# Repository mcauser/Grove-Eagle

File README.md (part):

# Grove-Eagle
[Eagle](http://www.cadsoftusa.com/) source files for [Grove](http://www.seeedstudio.com/wiki/GROVE_System) modules

Module | Latest | Wiki | Bazaar | SKU
:----- |:------ |:---- |:------ |:---
Grove - 125KHz RFID Reader | - | [Wiki](http://www.seeedstudio.com/wiki/Grove_-_125KHz_RFID_Reader) | [Buy](http://www.seeedstudio.com/depot/Grove-125KHz-RFID-Reader-p-1008.html) | SEN11425P
Grove - 2-Coil Latching Relay | v1.0b | [Wiki](http://www.seeedstudio.com/wiki/Grove_-_2-Coil_Latching_Relay) | [Buy](http://www.seeedstudio.com/depot/Grove-2Coil-Latching-Relay-p-1446.html) | COM05061P
Grove - 3-Axis Analog Accelerometer | v1.1 | [Wiki](http://www.seeedstudio.com/wiki/Grove_-_3-Axis_Analog_Accelerometer) | [Buy](http://www.seeedstudio.com/depot/Grove-3Axis-Analog-Accelerometer-p-1086.html) | SEN02241P
Grove - 3-Axis Digital Accelerometer(±1.5g) | v1.2b | [Wiki](http://www.seeedstudio.com/wiki/Grove_-_3-Axis_Digital_Accelerometer%28%C2%B11.5g%29) | [Buy](http://www.seeedstudio.com/depot/Grove-3Axis-Digital-Accelerometer15g-p-765.html) | SEN21853P
Grove - 3-Axis Digital Accelerometer(±16g) | v1.3 | [Wiki](http://www.seeedstudio.com/wiki/Grove_-_3-Axis_Digital_Accelerometer%28%C2%B116g%29) | [Buy](http://www.seeedstudio.com/depot/Grove-3Axis-Digital-Accelerometer16g-p-1156.html) | SEN04051P
Grove - 3-Axis Digital Accelerometer(±400g) | v1.0 | [Wiki](http://www.seeedstudio.com/wiki/Grove_-_3-Axis_Digital_Accelerometer%28%C2%B1400g%29) | [Buy](http://www.seeedstudio.com/depot/Grove-3Axis-Digital-Accelerometer400g-p-1897.html) | 811022001
Grove - 3-Axis Digital Compass | v1.2 | [Wiki](http://www.seeedstudio.com/wiki/Grove_-_3-Axis_Digital_Compass) | [Buy](http://www.seeedstudio.com/depot/Grove-3Axis-Digital-Compass-p-759.html) | SEN12753P
Grove - 3-Axis Digital Gyro | v1.2b | [Wiki](http://www.seeedstudio.com/wiki/Grove_-_3-Axis_Digital_Gyro) | [Buy](http://www.seeedstudio.com/depot/Grove-3Axis-Digital-Gyro-p-750.html) | SEN11763P
Grove - 315MHz Simple RF Link Kit | - | [Wiki](http://www.seeedstudio.com/wiki/Grove_-_315MHz_Simple_RF_Link_Kit) | [Buy](http://www.seeedstudio.com/depot/Grove-315MHz-Simple-RF-Link-Kit-p-1061.html) | WLS01051O
Grove - 4-Digit Display | v1.0 | [Wiki](http://www.seeedstudio.com/wiki/Grove_-_4-Digit_Display) | [Buy](http://www.seeedstudio.com/depot/Grove-4Digit-Display-p-1198.html) | LED05291P
Grove - 433MHz Simple RF Link Kit | - | [Wiki](http://www.seeedstudio.com/wiki/Grove_-_433MHz_Simple_RF_Link_Kit) | [Buy](http://www.seeedstudio.com/depot/Grove-433MHz-Simple-RF-link-kit-p-1062.html) | WLS01052O
Grove - 6-Axis Accelerometer and Compass | v2.0 | [Wiki](http://www.seeedstudio.com/wiki/Grove_-_6-Axis_Accelerometer%26Compass_V2.0) | [Buy](http://www.seeedstudio.com/depot/Grove-6Axis-AccelerometerCompass-p-1448.html) | SEN05072P
Grove - 80cm Infrared Proximity Sensor | - | [Wiki](http://www.seeedstudio.com/wiki/Grove_-_80cm_Infrared_Proximity_Sensor) | [Buy](http://www.seeedstudio.com/depot/Grove-80cm-Infrared-Proximity-Sensor-p-788.html) | SEN39046P
Grove - Air Quality Sensor | v1.3 | [Wiki](http://www.seeedstudio.com/wiki/Grove_-_Air_Quality_Sensor) | [Buy](http://www.seeedstudio.com/depot/Grove-Air-quality-sensor-p-1065.html) | SEN01111P
Grove - Alcohol Sensor | v1.2 | [Wiki](http://www.seeedstudio.com/wiki/Grove_-_Alcohol_Sensor) | [Buy](http://www.seeedstudio.com/depot/Grove-Alcohol-Sensor-p-764.html) | SEN21723P
Grove - Barometer (High-Accuracy) | v1.0 | [Wiki](http://www.seeedstudio.com/wiki/Grove_-_Barometer_%28High-Accuracy%29) | [Buy](http://www.seeedstudio.com/depot/Grove-Barometer-HighAccuracy-p-1865.html) | 811027001
Grove - Barometer Sensor (BMP180) | v1.0 | [Wiki](http://www.seeedstudio.com/wiki/Grove_-_Barometer_Sensor_%28BMP180%29) | [Buy](http://www.seeedstudio.com/depot/Grove-Barometer-SensorBMP180-p-1840.html) | 811024001
Grove - Barometer Sensor | v1.0b | [Wiki](http://www.seeedstudio.com/wiki/Grove_-_Barometer_Sensor) | [Buy](http://www.seeedstudio.com/depot/Grove-Barometer-Sensor-p-1199.html) | SEN05291P
Grove - Base Shield for IOIO-OTG | v1.0 | [Wiki](http://www.seeedstudio.com/wiki/Grove_-_Base_Shield_for_IOIO-OTG) | [Buy](http://www.seeedstudio.com/depot/Grove-Base-Shield-for-IOIOOTG-p-1613.html) | SLD00100P
Grove - Base Shield for NodeMCU | v1.0 | [Wiki](http://www.seeedstudio.com/wiki/Grove_Base_Shield_for_NodeMCU_V1.0) | [Buy](http://www.seeedstudio.com/depot/Grove-Base-Shield-for-NodeMCU-p-2513.html) | 105020008
Grove - Base Shield v1.2 | v1.2 | [Wiki](http://www.seeedstudio.com/wiki/Grove_-_Base_Shield_v1.2) | [Buy](http://www.seeedstudio.com/depot/Grove-Base-Shield-p-754.html) | SLD12148P
Grove - Base Shield v1.3 | v1.3 | [Wiki](http://www.seeedstudio.com/wiki/Grove_-_Base_Shield_V1.3) | [Buy](http://www.seeedstudio.com/depot/base-shield-v13-p-1378.html) | SLD01099P
Grove - Base Shield v2 | v2.0 | [Wiki](http://www.seeedstudio.com/wiki/Base_shield_v2) | [Buy](http://www.seeedstudio.com/depot/base-shield-v13-p-1378.html) | SLD01099P
Grove - Bee Socket | v0.9a | [Wiki](http://www.seeedstudio.com/wiki/Grove_-_Bee_Socket) | [Buy](http://www.seeedstudio.com/depot/Grove-Bee-Socket-p-1449.html) | COM05081P
Grove - BLE | v1.0 | [Wiki](http://www.seeedstudio.com/wiki/Grove_BLE_v1) | [Buy](http://www.seeedstudio.com/depot/Grove-BLE-p-1929.html) | 811007001
Grove - BLE (Dual Model) | v1.0 | [Wiki](http://www.seeedstudio.com/wiki/Grove_-_BLE_%28dual_model%29_v1.0) | [Buy](http://www.seeedstudio.com/depot/Grove-BLE-dual-model-p-2407.html) | 113020009
Grove - BlinkM | - | [Wiki](http://www.seeedstudio.com/wiki/Grove_-_BlinkM) | [Buy](http://www.seeedstudio.com/depot/Grove-BlinkM-p-826.html) | LED42149P
Grove - Blue LED | - | [Wiki](http://www.seeedstudio.com/wiki/Grove_-_LED) | [Buy](http://www.seeedstudio.com/depot/Grove-Blue-LED-p-1139.html) | COM04051P
Grove - Button | v1.0b | [Wiki](http://www.seeedstudio.com/wiki/Grove_-_Button) | [Buy](http://www.seeedstudio.com/depot/Grove-Button-p-766.html) | COM22242P
Grove - Button(P) | - | [Wiki](http://www.seeedstudio.com/wiki/Grove_-_Button) | [Buy](http://www.seeedstudio.com/depot/Grove-ButtonP-p-1243.html) | COM08211P
Grove - Buzzer | v1.1b | [Wiki](http://www.seeedstudio.com/wiki/Grove_-_Buzzer) | [Buy](http://www.seeedstudio.com/depot/Grove-Buzzer-p-768.html) | COM22458P
Grove - Chainable RGB LED | v0.9b | [Wiki](http://www.seeedstudio.com/wiki/Grove_-_Chainable_RGB_LED) | [Buy](http://www.seeedstudio.com/depot/Grove-Chainable-RGB-LED-p-850.html) | COM53140P
Grove - Chest Strap Heart Rate Sensor | v1.0 | [Wiki](http://www.seeedstudio.com/wiki/Grove_-_Chest_Strap_Heart_Rate_Sensor) | [Buy](http://www.seeedstudio.com/depot/Grove-Chest-Strap-Heart-Rate-Sensor-p-1115.html) | MED03211P
Grove - Circular LED | v0.9b | [Wiki](http://www.seeedstudio.com/wiki/Grove_-_Circular_LED) | [Buy](http://www.seeedstudio.com/depot/Grove-Circular-LED-p-1353.html) | LED01113P
Grove - CO2 Sensor | - | [Wiki](http://www.seeedstudio.com/wiki/Grove_-_CO2_Sensor) | [Buy](http://www.seeedstudio.com/depot/Grove-CO2-Sensor-p-1863.html) | 101020067
Grove - Collision Sensor | v2.0 | [Wiki](http://www.seeedstudio.com/wiki/Grove_-_Collision_Sensor) | [Buy](http://www.seeedstudio.com/depot/Grove-Collision-Sensor-p-1132.html) | SEN03281P
Grove - Differential Amplifier | v1.2 | [Wiki](http://www.seeedstudio.com/wiki/Grove_-_Differential_Amplifier) | [Buy](http://www.seeedstudio.com/depot/Grove-Differential-Amplifier-p-1284.html) | COM10221P
Grove - Digital Infrared Temperature Sensor | v1.0 | [Wiki](http://www.seeedstudio.com/wiki/Grove_-_Digital_Infrared_Temperature_Sensor) | [Buy](http://www.seeedstudio.com/depot/Grove-Digital-Infrared-Temperature-Sensor-p-2385.html) | 101020077
Grove - Digital Light Sensor | v0.9b | [Wiki](http://www.seeedstudio.com/wiki/Grove_-_Digital_Light_Sensor) | [Buy](http://www.seeedstudio.com/depot/Grove-Digital-Light-Sensor-p-1281.html) | SEN10171P
Grove - DMX512 | v1.0 | [Wiki](http://www.seeedstudio.com/wiki/Grove_-_DMX512) | [Buy](http://www.seeedstudio.com/depot/Grove-DMX512-p-1447.html) | ACC05071P
Grove - Dry-Reed Relay | v1.0b | [Wiki](http://www.seeedstudio.com/wiki/Grove_-_Dry-Reed_Relay) | [Buy](http://www.seeedstudio.com/depot/Grove-DryReed-Relay-p-1412.html) | COM04071P
Grove - Dust Sensor | - | [Wiki](http://www.seeedstudio.com/wiki/Grove_-_Dust_Sensor) | [Buy](http://www.seeedstudio.com/depot/Grove-Dust-Sensor-p-1050.html) | SEN12291P
Grove - Ear-clip Heart Rate Sensor | - | [Wiki](http://www.seeedstudio.com/wiki/Grove_-_Ear-clip_Heart_Rate_Sensor) | [Buy](http://www.seeedstudio.com/depot/Grove-Earclip-Heart-Rate-Sensor-p-1116.html) | MED03212P
Grove - Electricity Sensor | v1.0 | [Wiki](http://www.seeedstudio.com/wiki/Grove_-_Electricity_Sensor) | [Buy](http://www.seeedstudio.com/depot/Grove-Electricity-Sensor-p-777.html) | SEN23931P
Grove - Electromagnet | v1.0 | [Wiki](http://www.seeedstudio.com/wiki/Grove_-_Electromagnet) | [Buy](http://www.seeedstudio.com/depot/Grove-Electromagnet-p-1820.html) | 811014001
Grove - EL Driver | v1.0 | [Wiki](http://www.seeedstudio.com/wiki/Grove_-_EL_Driver) | [Buy](http://www.seeedstudio.com/depot/GroveEL-Driver-p-2269.html) | 105020005
Grove - EMG Detector | v1.1 | [Wiki](http://www.seeedstudio.com/wiki/Grove_-_EMG_Detector) | [Buy](http://www.seeedstudio.com/depot/Grove-EMG-Detector-p-1737.html) | 811006001
Grove - Encoder | v0.9b | [Wiki](http://www.seeedstudio.com/wiki/Grove_-_Encoder) | [Buy](http://www.seeedstudio.com/depot/Grove-Encoder-p-1352.html) | COM01112P
Grove - Finger-clip Heart Rate Sensor | v1.0 | [Wiki](http://www.seeedstudio.com/wiki/Grove_-_Finger-clip_Heart_Rate_Sensor) | [Buy](http://www.seeedstudio.com/depot/Grove-Fingerclip-Heart-Rate-Sensor-p-2425.html) | 103020024
Grove - Fingerprint Sensor | - | [Wiki](http://www.seeedstudio.com/wiki/Grove_-_Fingerprint_Sensor) | [Buy](http://www.seeedstudio.com/depot/Grove-Fingerprint-Sensor-p-1424.html) | SEN04172P
Grove - Flame Sensor | v1.0 | [Wiki](http://www.seeedstudio.com/wiki/Grove_-_Flame_Sensor) | [Buy](http://www.seeedstudio.com/depot/Grove-Flame-Sensor-p-1450.html) | SEN05082P
Grove - FM Receiver | v1.0 | [Wiki](http://www.seeedstudio.com/wiki/Grove_-_FM_Receiver) | [Buy](http://www.seeedstudio.com/depot/Grove-FM-Receiver-p-1841.html) | 811021001
Grove - Gas Sensor(MQ2) | v1.4 | [Wiki](http://www.seeedstudio.com/wiki/Grove_-_Gas_Sensor%28MQ2%29) | [Buy](http://www.seeedstudio.com/depot/Grove-Gas-SensorMQ2-p-937.html) | SEN90512P
Grove - Gas Sensor(MQ3) | v1.4 | [Wiki](http://www.seeedstudio.com/wiki/Grove_-_Gas_Sensor) | [Buy](http://www.seeedstudio.com/depot/Grove-Gas-SensorMQ3-p-1418.html) | SEN04091P
Grove - Gas Sensor(MQ5) | v1.4 | [Wiki](http://www.seeedstudio.com/wiki/Grove_-_Gas_Sensor%28MQ5%29) | [Buy](http://www.seeedstudio.com/depot/Grove-Gas-SensorMQ5-p-938.html) | SEN90502P
Grove - Gas Sensor(MQ9) | v1.4 | [Wiki](http://www.seeedstudio.com/wiki/Grove_-_Gas_Sensor) | [Buy](http://www.seeedstudio.com/depot/Grove-Gas-SensorMQ9-p-1419.html) | SEN04092P
Grove - Gas Sensor(O2) | v1.0 | [Wiki](http://www.seeedstudio.com/wiki/Grove_-_Gas_Sensor%28O%E2%82%82%29) | [Buy](http://www.seeedstudio.com/depot/Grove-Gas-SensorO2-p-1541.html) | SEN00500P
Grove - Geiger Counter | v0.9b | [Wiki](http://www.seeedstudio.com/wiki/Grove_-_Geiger_Counter) | [Buy](http://www.seeedstudio.com/depot/Grove-Geiger-Counter-p-867.html) | SEN63024P
Grove - Gesture | v1.0 | [Wiki](http://www.seeedstudio.com/wiki/Grove_-_Gesture_v1.0) | [Buy](http://www.seeedstudio.com/depot/Grove-Gesture-p-2463.html) | 101020083
Grove - GPS | v1.1 | [Wiki](http://www.seeedstudio.com/wiki/Grove_-_GPS) | [Buy](http://www.seeedstudio.com/depot/Grove-GPS-p-959.html) | SEN10752P
Grove - Green LED | - | [Wiki](http://www.seeedstudio.com/wiki/Grove_-_LED) | [Buy](http://www.seeedstudio.com/depot/Grove-Green-LED-p-1144.html) | COM04053P
Grove - GSR Sensor | v1.0 | [Wiki](http://www.seeedstudio.com/wiki/Grove_-_GSR_Sensor) | [Buy](http://www.seeedstudio.com/depot/Grove-GSR-p-1614.html) | SEN01400P
Grove - Hall Sensor | v0.9b | [Wiki](http://www.seeedstudio.com/wiki/Grove_-_Hall_Sensor) | [Buy](http://www.seeedstudio.com/depot/Grove-Hall-Sensor-p-965.html) | SEN14034P
Grove - Haptic Motor | v0.9 | [Wiki](http://www.seeedstudio.com/wiki/Grove_-_Haptic_Motor) | [Buy](http://www.seeedstudio.com/depot/Grove%C2%A0%C2%A0Haptic%C2%A0Motor-p-2546.html) | 105020011
Grove - HCHO Sensor | v1.0 | [Wiki](http://www.seeedstudio.com/wiki/Grove_-_HCHO_Sensor) | [Buy](http://www.seeedstudio.com/depot/Grove-HCHO-Sensor-p-1593.html) | SEN01500P
Grove - High Temperature Sensor | v1.0 | [Wiki](http://www.seeedstudio.com/wiki/Grove_-_High_Temperature_Sensor) | [Buy](http://www.seeedstudio.com/depot/Grove-High-Temperature-Sensor-p-1810.html) | 811010001
Grove - I2C ADC | v1.0 | [Wiki](http://www.seeedstudio.com/wiki/Grove_-_I2C_ADC) | [Buy](http://www.seeedstudio.com/depot/Grove-I2C-ADC-p-1580.html) | INT00100P
Grove - I2C Color Sensor | v1.2 | [Wiki](http://www.seeedstudio.com/wiki/Grove_-_I2C_Color_Sensor) | [Buy](http://www.seeedstudio.com/depot/Grove-I2C-Color-Sensor-p-854.html) | SEN60256P
Grove - I2C FM Receiver | v1.1 | [Wiki](http://www.seeedstudio.com/wiki/Grove_-_I2C_FM_Receiver) | [Buy](http://www.seeedstudio.com/depot/Grove-I2C-FM-Receiver-p-1953.html) | 107020006
Grove - I2C Hub | v1.1 | [Wiki](http://www.seeedstudio.com/wiki/Grove_-_I2C_Hub) | [Buy](http://www.seeedstudio.com/depot/Grove-I2C-Hub-p-851.html) | ACC53133P
Grove - I2C Motor Driver | v1.2 | [Wiki](http://www.seeedstudio.com/wiki/Grove_-_I2C_Motor_Driver) | [Buy](http://www.seeedstudio.com/depot/Grove-I2C-Motor-Driver-p-907.html) | ROB72212P
Grove - I2C Touch Sensor | v1.1 | [Wiki](http://www.seeedstudio.com/wiki/Grove_-_I2C_Touch_Sensor) | [Buy](http://www.seeedstudio.com/depot/Grove-I2C-Touch-Sensor-p-840.html) | SEN51153P
Grove - IMU 9DOF | v2.0 | [Wiki](http://www.seeedstudio.com/wiki/Grove_-_IMU_9DOF) | [Buy](http://www.seeedstudio.com/depot/Grove-IMU-9DOF-p-1728.html) | 811003001
Grove - IMU 10DOF | v1.1 | [Wiki](http://www.seeedstudio.com/wiki/Grove_-_IMU_10DOF) | http://www.seeedstudio.com/depot/Grove-IMU-10DOF-p-2386.html | 101020079
Grove - Infrared Emitter | v1.1 | [Wiki](http://www.seeedstudio.com/wiki/Grove_-_Infrared_Emitter) | [Buy](http://www.seeedstudio.com/depot/Grove-Infrared-Emitter-p-993.html) | WLS12148P
Grove - Infrared Receiver | v1.0 | [Wiki](http://www.seeedstudio.com/wiki/Grove_-_Infrared_Receiver) | [Buy](http://www.seeedstudio.com/depot/Grove-Infrared-Receiver-p-994.html) | WLS12136P
Grove - Infrared Reflective Sensor | v1.0 | [Wiki](http://www.seeedstudio.com/wiki/Grove_-_Infrared_Reflective_Sensor) | [Buy](http://www.seeedstudio.com/depot/Grove-Infrared-Reflective-Sensor-p-1230.html) | WLS07061P
Grove - Infrared temperature sensor | v1.0 | [Wiki](http://www.seeedstudio.com/wiki/Grove_-_Infrared_temperature_sensor) | [Buy](http://www.seeedstudio.com/depot/Grove-Infrared-Temperature-Sensor-p-1058.html) | SEN01041P
Grove - IR Distance Interrupter | v1.0 | [Wiki](http://www.seeedstudio.com/wiki/Grove_-_IR_Distance_Interrupt) | [Buy](http://www.seeedstudio.com/depot/Grove-IR-Distance-Interrupter-p-1278.html) | SEN09281P
Grove - Joint | v2.0 | [Wiki](http://www.seeedstudio.com/wiki/Grove_-_Joint_v2.0) | - | -
Grove - LCD RGB Backlight | - | [Wiki](http://www.seeedstudio.com/wiki/Grove_-_LCD_RGB_Backlight) | [Buy](http://www.seeedstudio.com/depot/Grove-LCD-RGB-Backlight-p-1643.html) | 811004001
Grove - LED Bar | v1.0 | [Wiki](http://www.seeedstudio.com/wiki/Grove_-_LED_Bar) | [Buy](http://www.seeedstudio.com/depot/Grove-LED-Bar-p-1178.html) | LED05031P
Grove - LED Socket Kit | v1.3 | [Wiki](http://www.seeedstudio.com/wiki/Grove_-_LED_Socket_Kit) | [Buy](http://www.seeedstudio.com/depot/Grove-LED-p-767.html) | COM22341P
Grove - LED String Light | v1.0 | [Wiki](http://www.seeedstudio.com/wiki/Grove_-_LED_String_Light) | [Buy](http://www.seeedstudio.com/depot/Grove-LED-String-Light-p-1821.html) | 811019001
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
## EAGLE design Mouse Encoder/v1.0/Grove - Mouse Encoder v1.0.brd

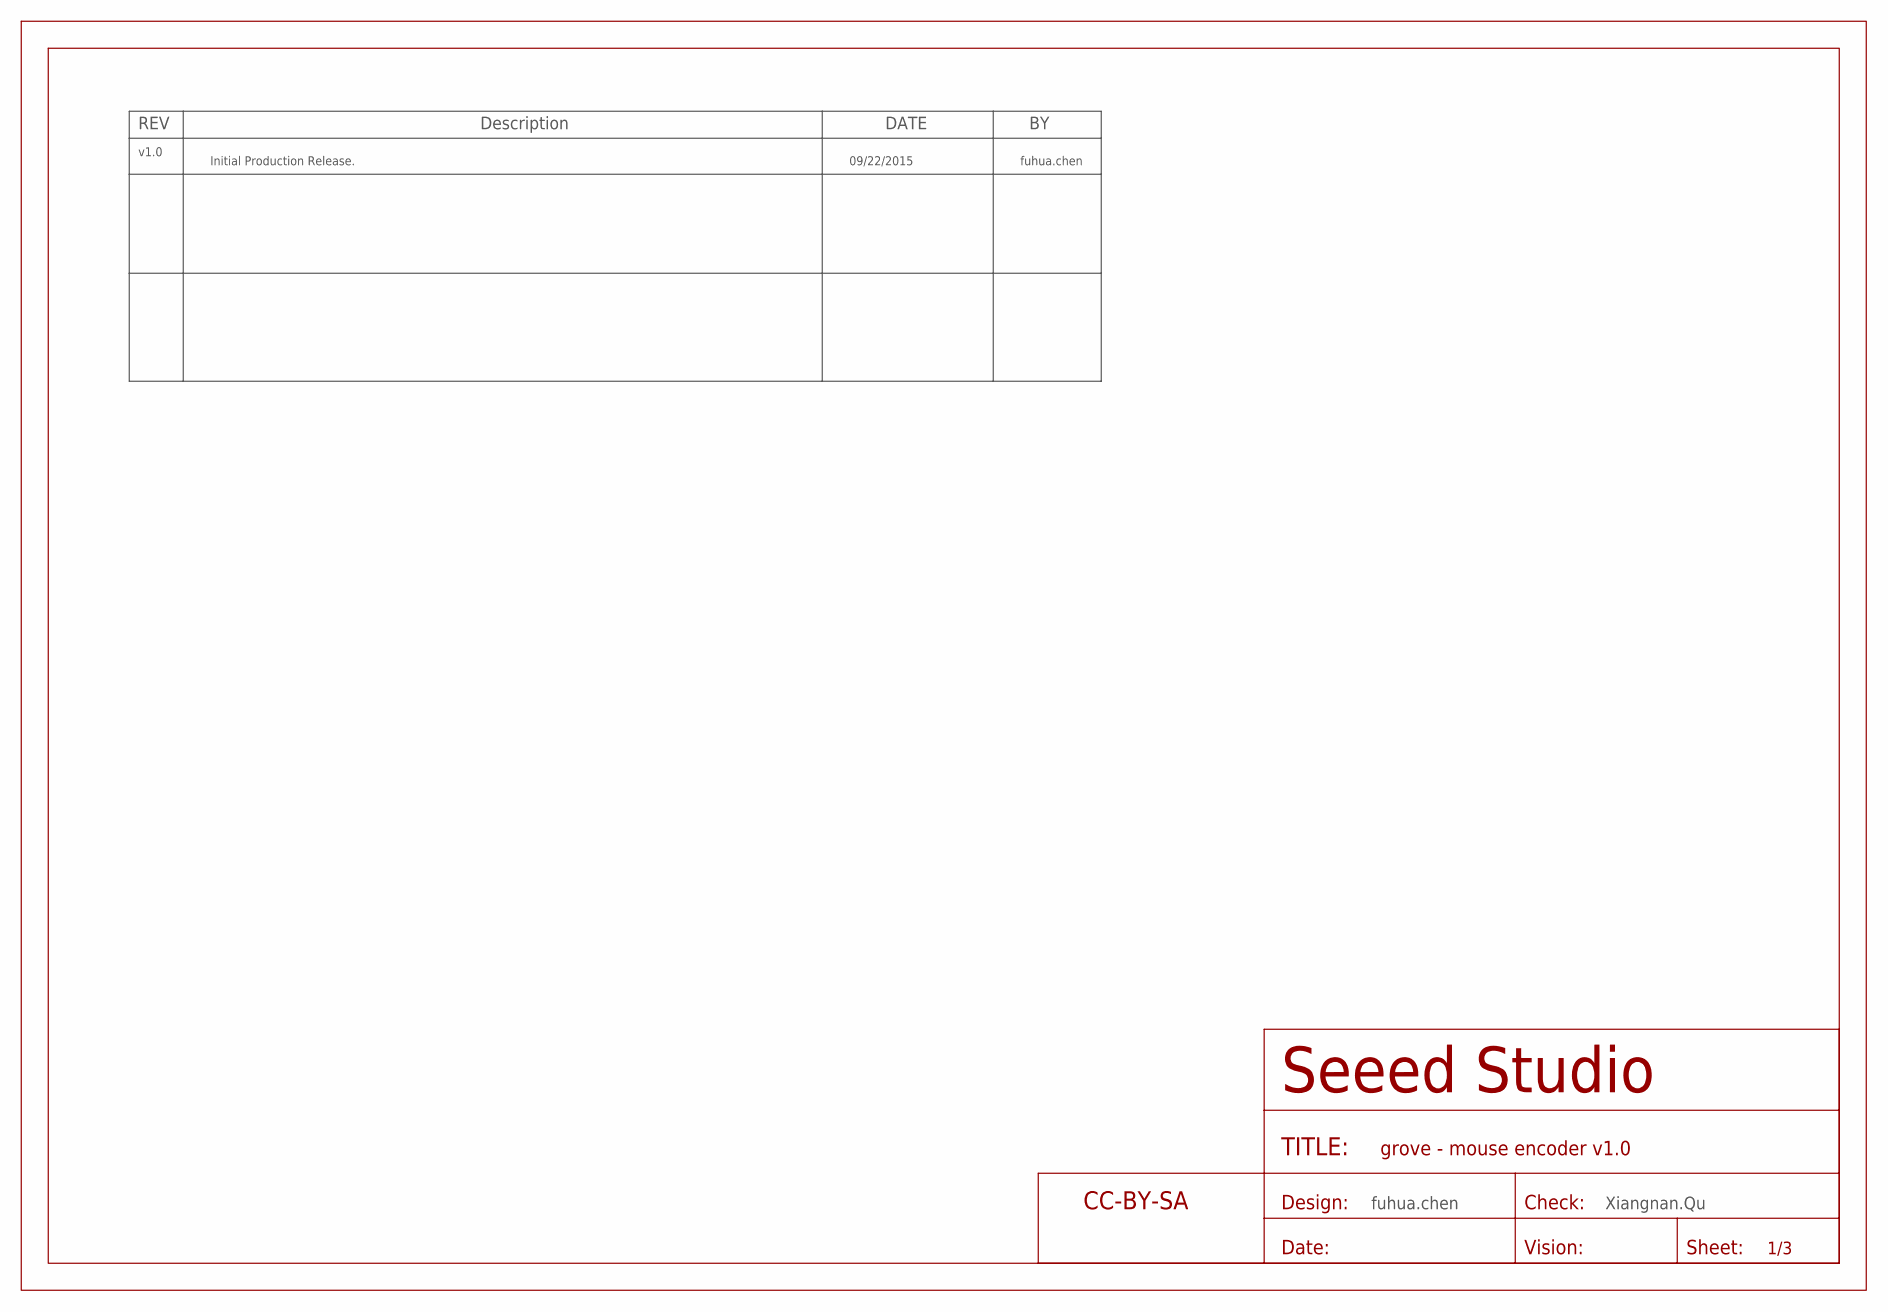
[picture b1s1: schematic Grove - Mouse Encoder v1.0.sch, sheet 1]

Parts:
U$5: SEEEDSTUDIO-OPEN-SCH-FRAME; SEEEDSTUDIO-PCB-FRAME

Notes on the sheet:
fuhua.chen
Xiangnan.Qu
REV
Description
DATE
v1.0
09/22/2015
Initial Production Release.

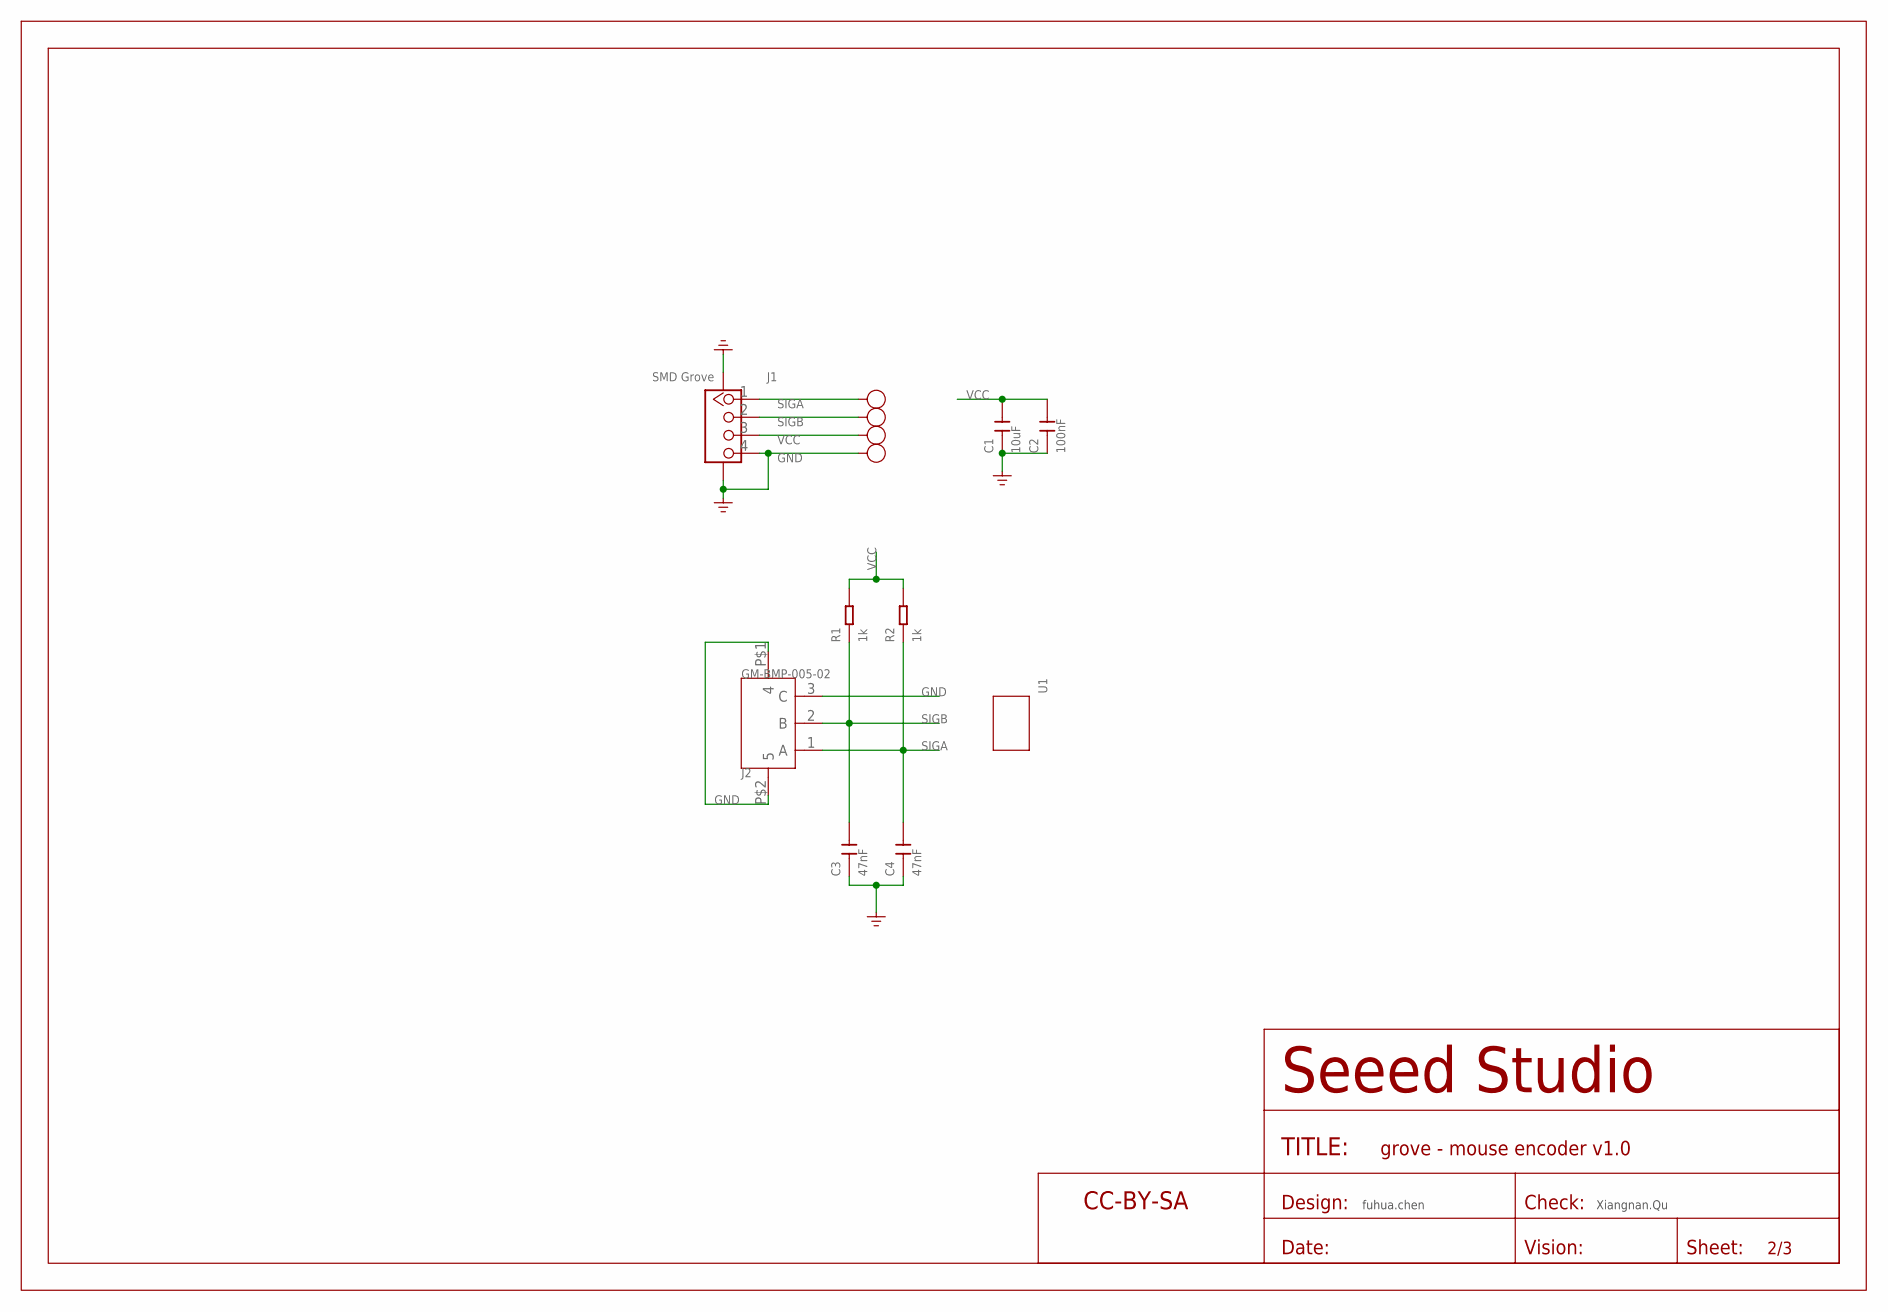
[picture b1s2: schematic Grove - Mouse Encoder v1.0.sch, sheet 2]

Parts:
C1: 10uF; C0603
C2: 100nF; C0603
C3, C4: 47nF; C0603
FR1: SEEEDSTUDIO-OPEN-SCH-FRAME; SEEEDSTUDIO-PCB-FRAME
GND: GND; TP-D45MIL
J1: SMD Grove; HW4-SMD-2.0-90D
J2: GM-BMP-005-02; DIP5-2.5-10.8X6.8X11.1MM
R1, R2: 1k; R0603
SIGA: SIGA; TP-D45MIL
SIGB: SIGB; TP-D45MIL
U1: GROVE'1U'; GROVE-1X1-TEST-PLATFORM
VCC: VCC; TP-D45MIL

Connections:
GND: C1.1, C2.1, C3.1, C4.1, GND.T, J1.4, J1.SS1, J1.SS2, J2.3 (C), J2.P$1 (4), J2.P$2 (5)
SIGA: C4.2, J1.1, J2.1 (A), R2.1, SIGA.T
SIGB: C3.2, J1.2, J2.2 (B), R1.1, SIGB.T
VCC: C1.2, C2.2, J1.3, R1.2, R2.2, VCC.T

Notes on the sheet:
fuhua.chen
Xiangnan.Qu

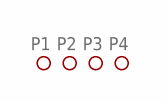
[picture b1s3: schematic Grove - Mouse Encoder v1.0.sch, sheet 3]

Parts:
P1, P2, P3, P4: PAD-MARK'ANNULAR'; ROUND-MARK-1.0

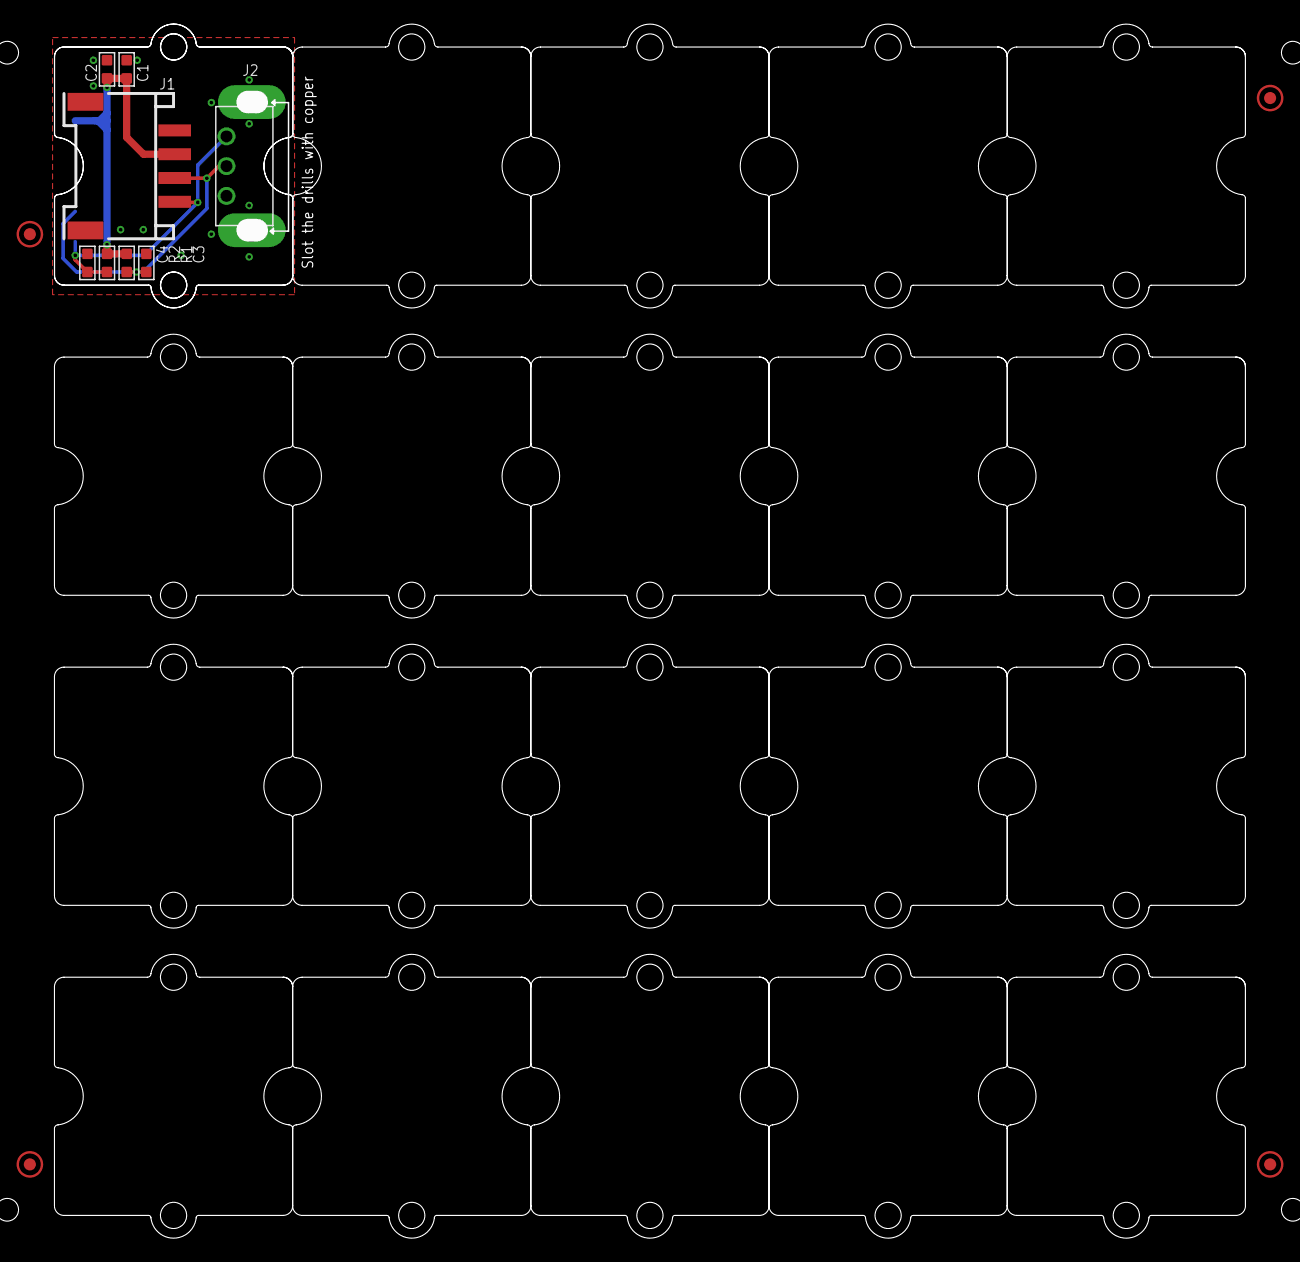
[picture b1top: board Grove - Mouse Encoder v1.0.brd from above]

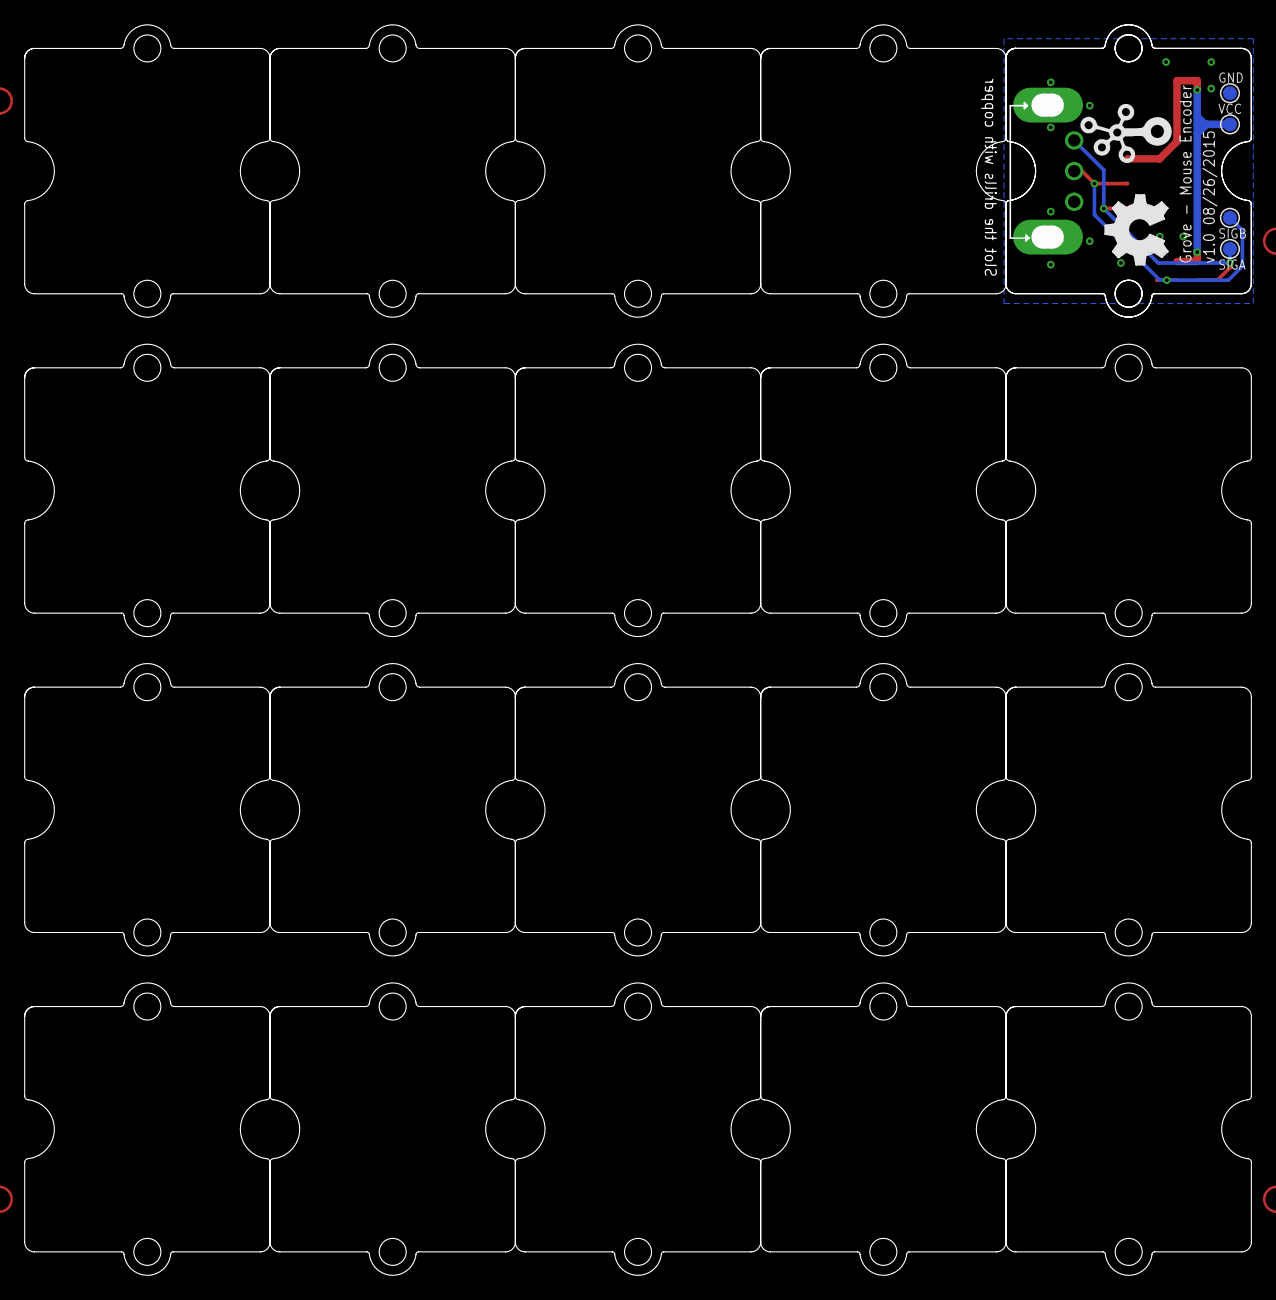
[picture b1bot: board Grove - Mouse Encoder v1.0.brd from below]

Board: 2 copper layers, 100.0 x 102.0 mm, 41 parts (6 on the bottom side), 4 nets.

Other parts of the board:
U$1: OSHW_FILLX200_NOTEXT
U$2: GROVE-SILK-BIG
U$3, U$4, U$7, U$8, U$9, U$10, U$11, U$12, U$13, U$14, U$15, U$16, U$17, U$18, U$19, U$20, U$21, U$22, U$23, U$24: GROVE-1*1-TEST-PLATFORM

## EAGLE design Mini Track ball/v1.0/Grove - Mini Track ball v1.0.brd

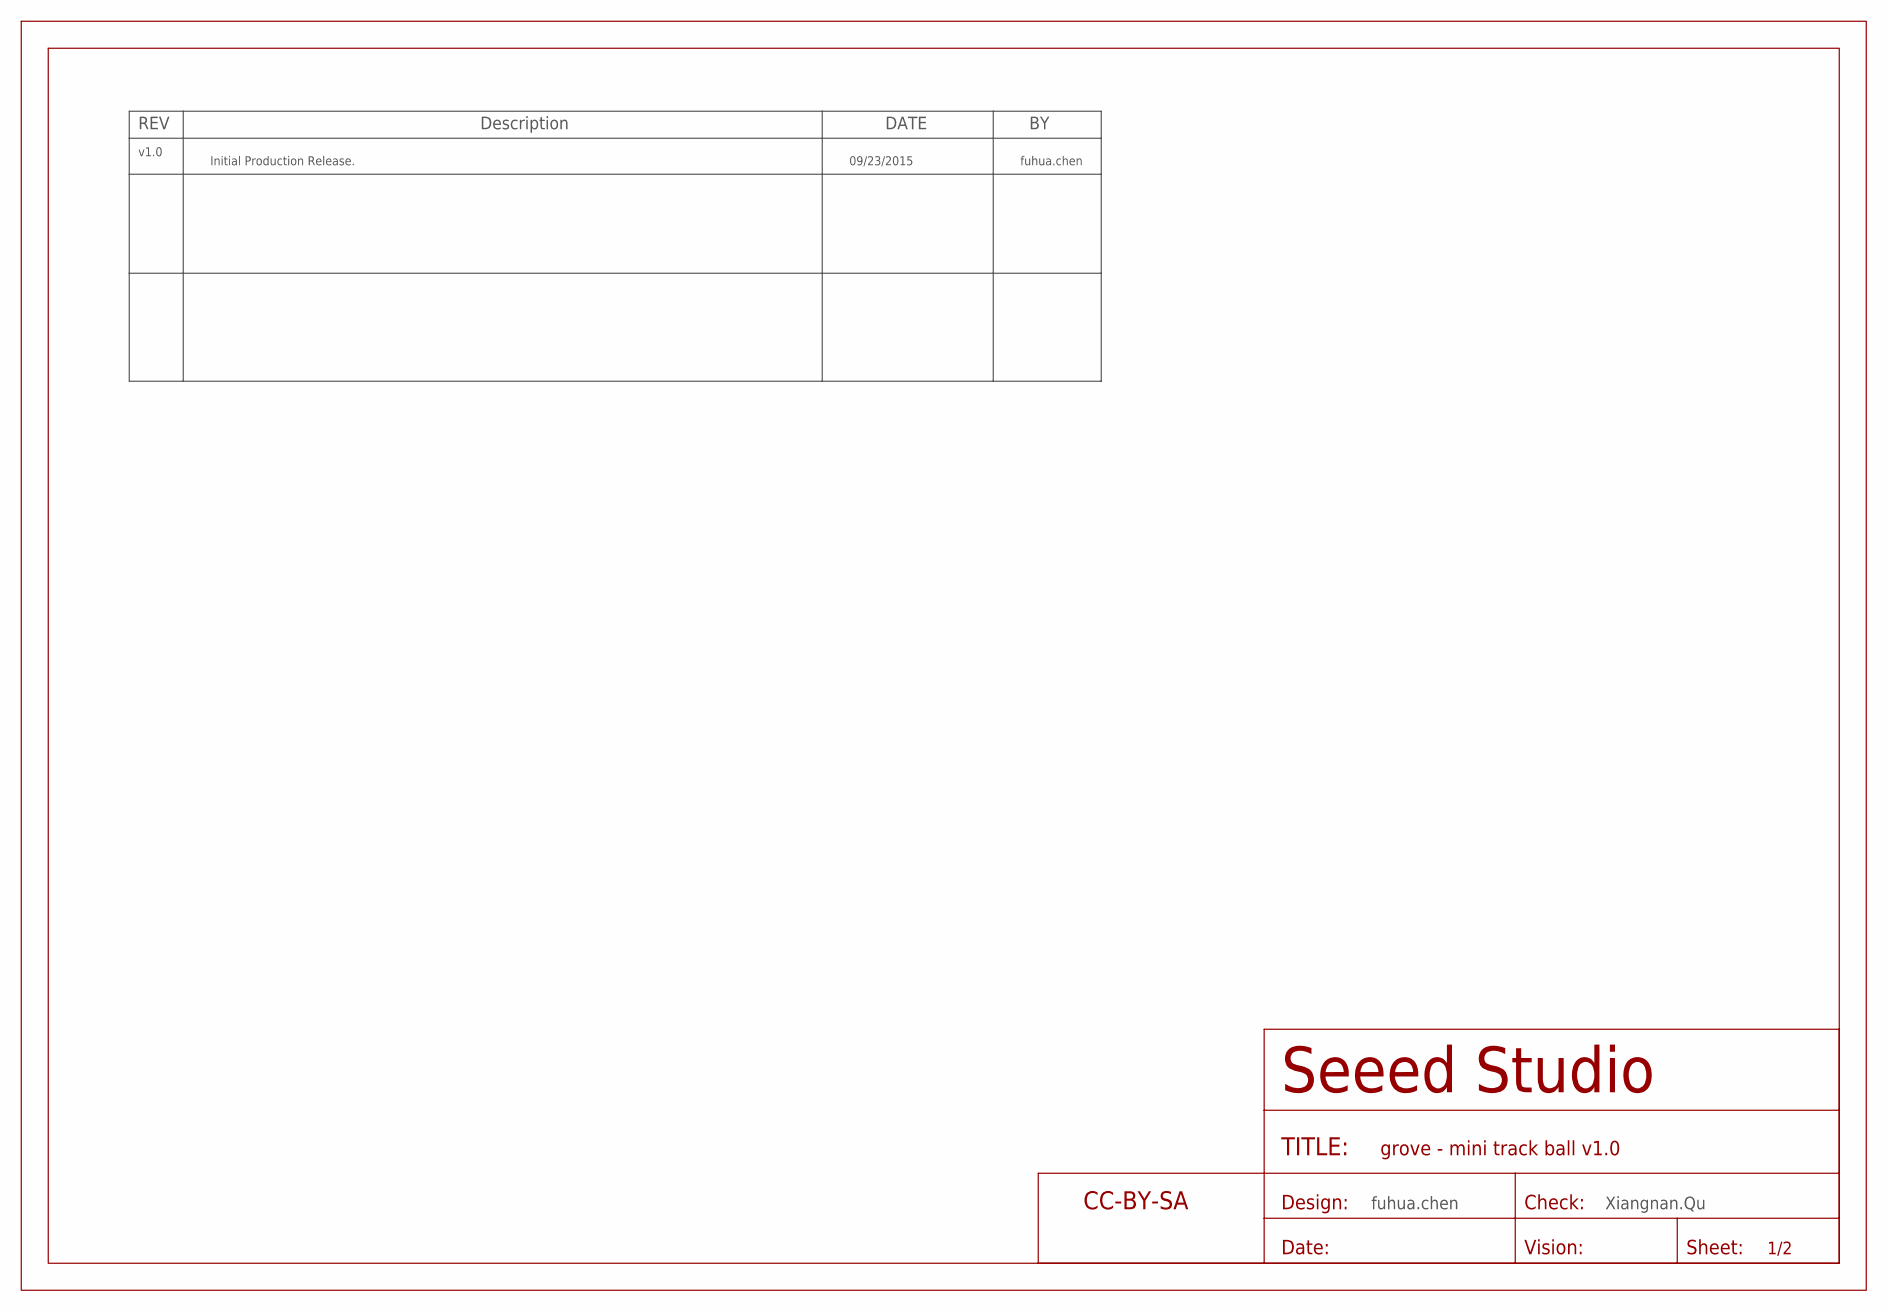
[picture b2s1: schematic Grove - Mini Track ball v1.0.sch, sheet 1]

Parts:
U$13: SEEEDSTUDIO-OPEN-SCH-FRAME; SEEEDSTUDIO-PCB-FRAME

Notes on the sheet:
fuhua.chen
Xiangnan.Qu
REV
Description
DATE
v1.0
09/23/2015
Initial Production Release.

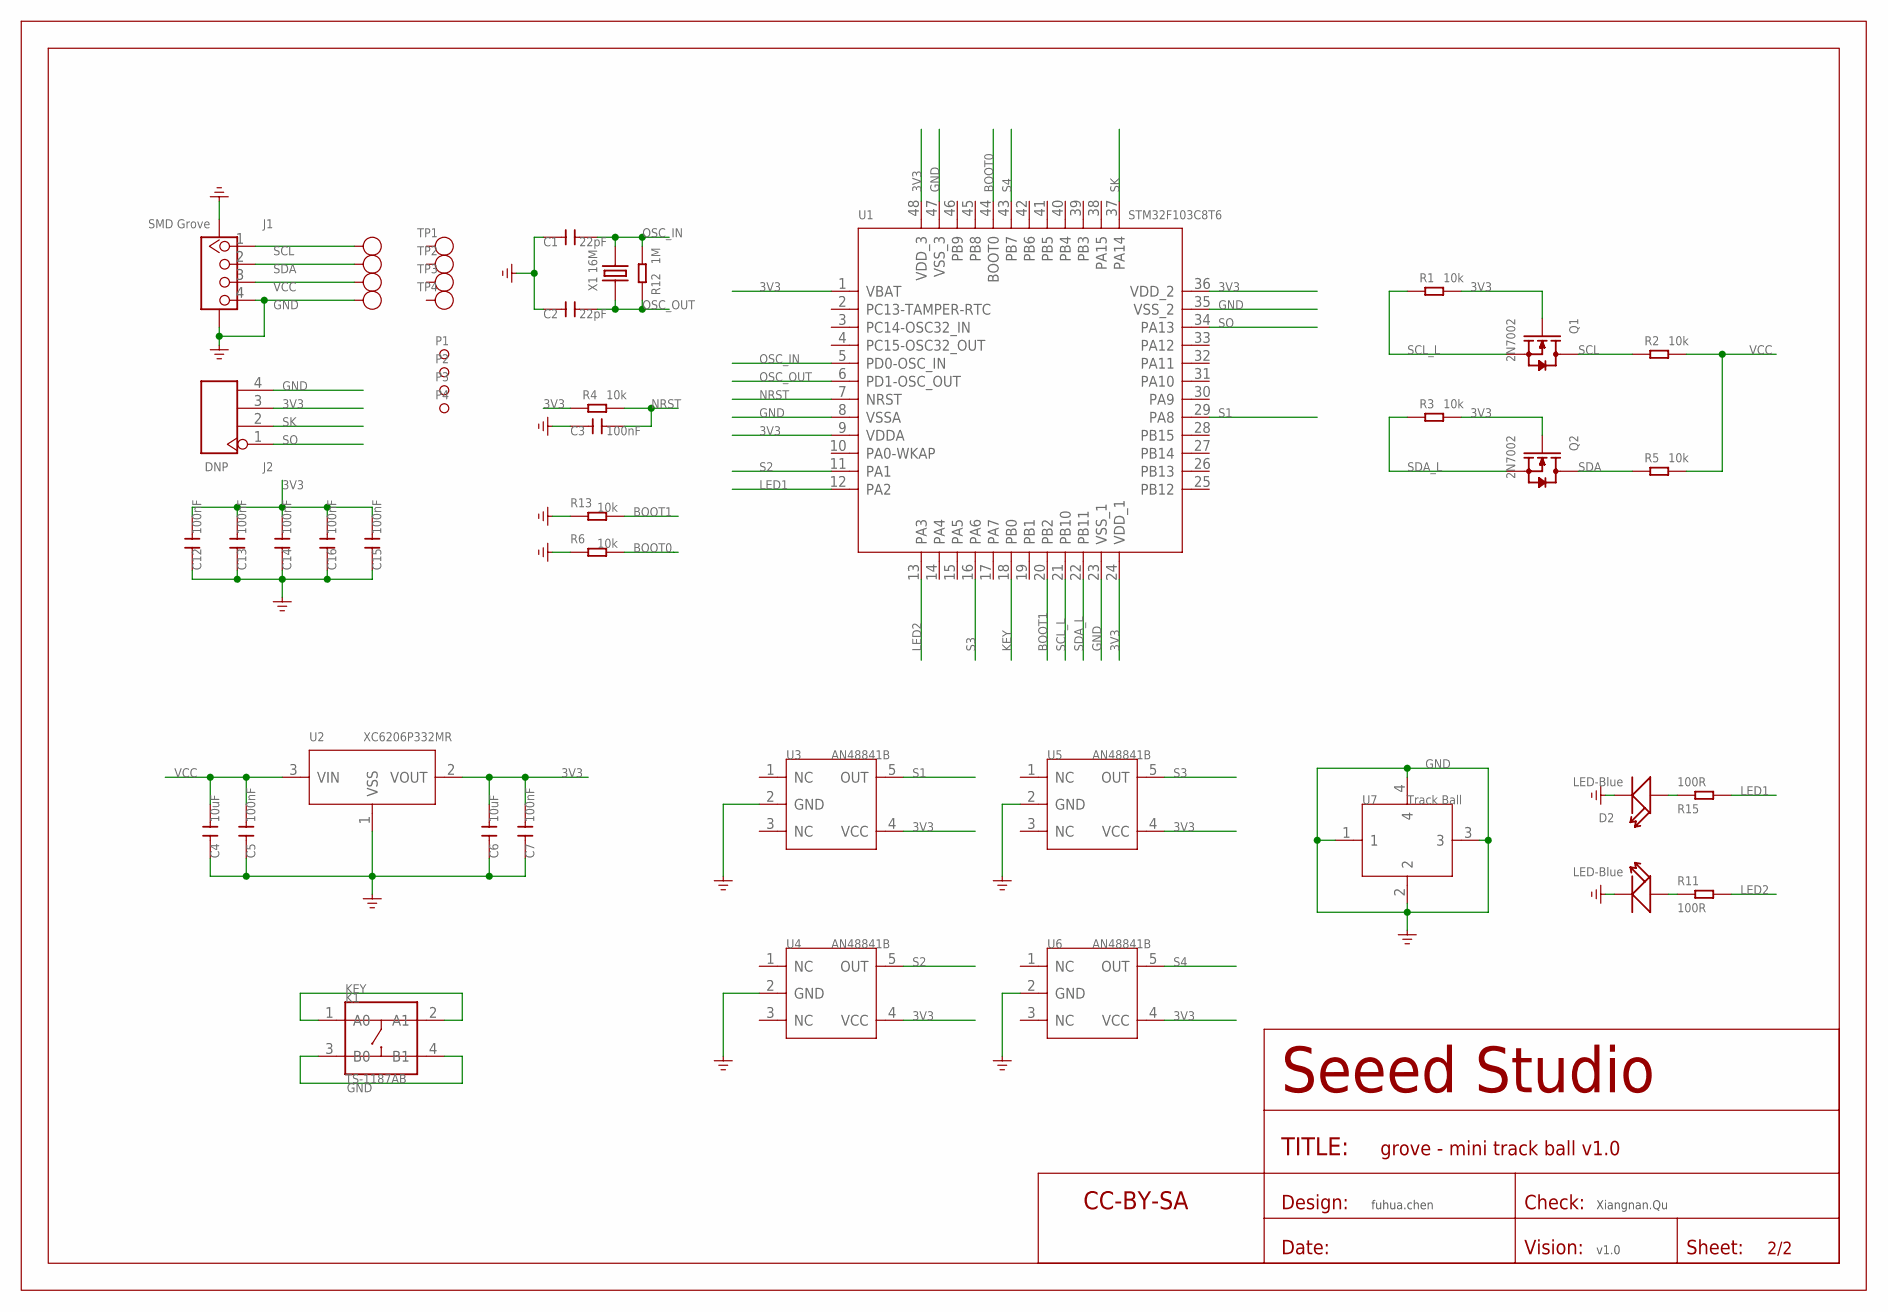
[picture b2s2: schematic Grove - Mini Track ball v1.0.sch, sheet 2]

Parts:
C1, C2: 22pF; C0402
C3, C5, C7, C12, C13, C14, C15, C16: 100nF; C0402
C4, C6: 10uF; C0402
D1, D2: LED-Blue; LED-0402
FR: SEEEDSTUDIO-OPEN-SCH-FRAME; SEEEDSTUDIO-PCB-FRAME
GND: GND; TP-D45MIL
J1: SMD Grove; HW4-SMD-2.0-90D
J2: DNP; H4-2.54
K1: TS-1187AB; SW4-4.5X4.5X0.5MM
P1, P2, P3, P4: MARK-1.0'ANNULAR'; ROUND-MARK-1.0
Q1, Q2: 2N7002; SOT-23
R1, R2, R3, R4, R5, R6, R13: 10k; R0402
R11, R15: 100R; R0402
R12: 1M; R0402
SCL: SCL; TP-D45MIL
SDA: SDA; TP-D45MIL
TP1, TP2, TP3, TP4: TEST-POINT'4545'; TP-D45MIL
U1: STM32F103C8T6; LQFP48
U2: XC6206P332MR; SOT-23
U3, U4, U5, U6: AN48841B; SMINI-5DE
U7: Track Ball; BALL4P-9.1X9.1X6.04MM
VCC: VCC; TP-D45MIL
X1: 16M; X4-SMD-3.2X2.5X0.7MM

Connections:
3V3: C6.2, C7.2, C12.2, C13.2, C14.2, C15.2, C16.2, J2.3, Q1.1 (G), Q2.1 (G), R1.2, R3.2, R4.1, U1.1 (VBAT), U1.9 (VDDA), U1.24 (VDD_1), U1.36 (VDD_2), U1.48 (VDD_3), U2.2 (VOUT), U3.4 (VCC), U4.4 (VCC), U5.4 (VCC), U6.4 (VCC)
BOOT0: R6.2, U1.44 (BOOT0)
BOOT1: R13.2, U1.20 (PB2)
GND: C1.1, C2.1, C3.1, C4.1, C5.1, C6.1, C7.1, C12.1, C13.1, C14.1, C15.1, C16.1, D1.-, D2.-, GND.T, J1.4, J1.SS1, J1.SS2, J2.4, K1.3 (B0), K1.4 (B1), R6.1, R13.1, U1.8 (VSSA), U1.23 (VSS_1), U1.35 (VSS_2), U1.47 (VSS_3), U2.1 (VSS), U3.2 (GND), U4.2 (GND), U5.2 (GND), U6.2 (GND), U7.1, U7.2, U7.3, U7.4
KEY: K1.1 (A0), K1.2 (A1), U1.18 (PB0)
LED1: R15.2, U1.12 (PA2)
LED2: R11.2, U1.13 (PA3)
unnamed: D1.+, R11.1
unnamed: D2.+, R15.1
NRST: C3.2, R4.2, U1.7 (NRST)
OSC_IN: C1.2, R12.2, U1.5 (PD0-OSC_IN), X1.4 (2)
OSC_OUT: C2.2, R12.1, U1.6 (PD1-OSC_OUT), X1.2 (1)
S1: U1.29 (PA8), U3.5 (OUT)
S2: U1.11 (PA1), U4.5 (OUT)
S3: U1.16 (PA6), U5.5 (OUT)
S4: U1.43 (PB7), U6.5 (OUT)
SCL: J1.1, Q1.3 (D), R2.1, SCL.T
SCL_L: Q1.2 (S), R1.1, U1.21 (PB10)
SDA: J1.2, Q2.3 (D), R5.1, SDA.T
SDA_L: Q2.2 (S), R3.1, U1.22 (PB11)
SK: J2.2, U1.37 (PA14)
SO: J2.1, U1.34 (PA13)
VCC: C4.2, C5.2, J1.3, R2.2, R5.2, U2.3 (VIN), VCC.T

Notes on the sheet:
fuhua.chen
v1.0
Xiangnan.Qu

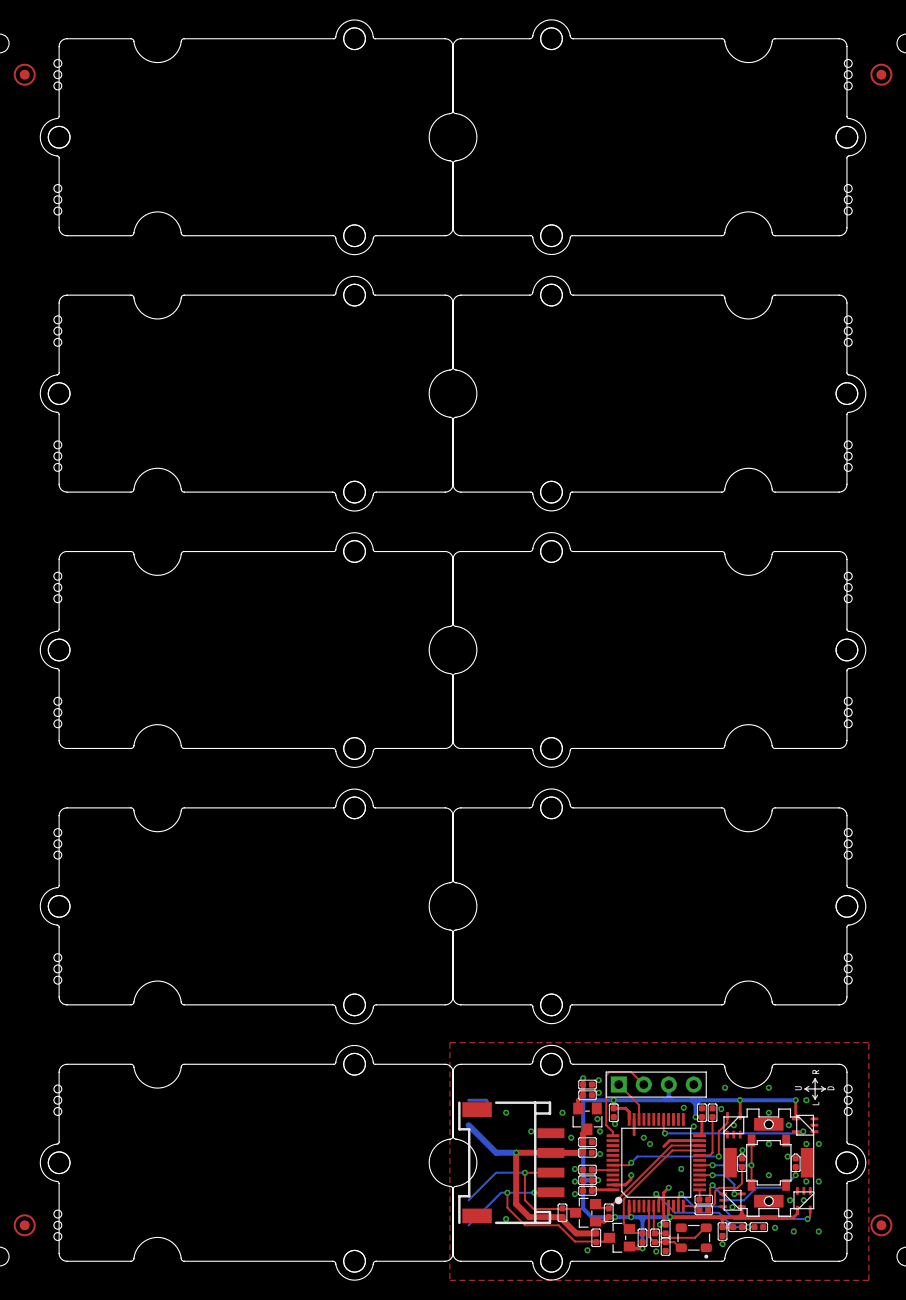
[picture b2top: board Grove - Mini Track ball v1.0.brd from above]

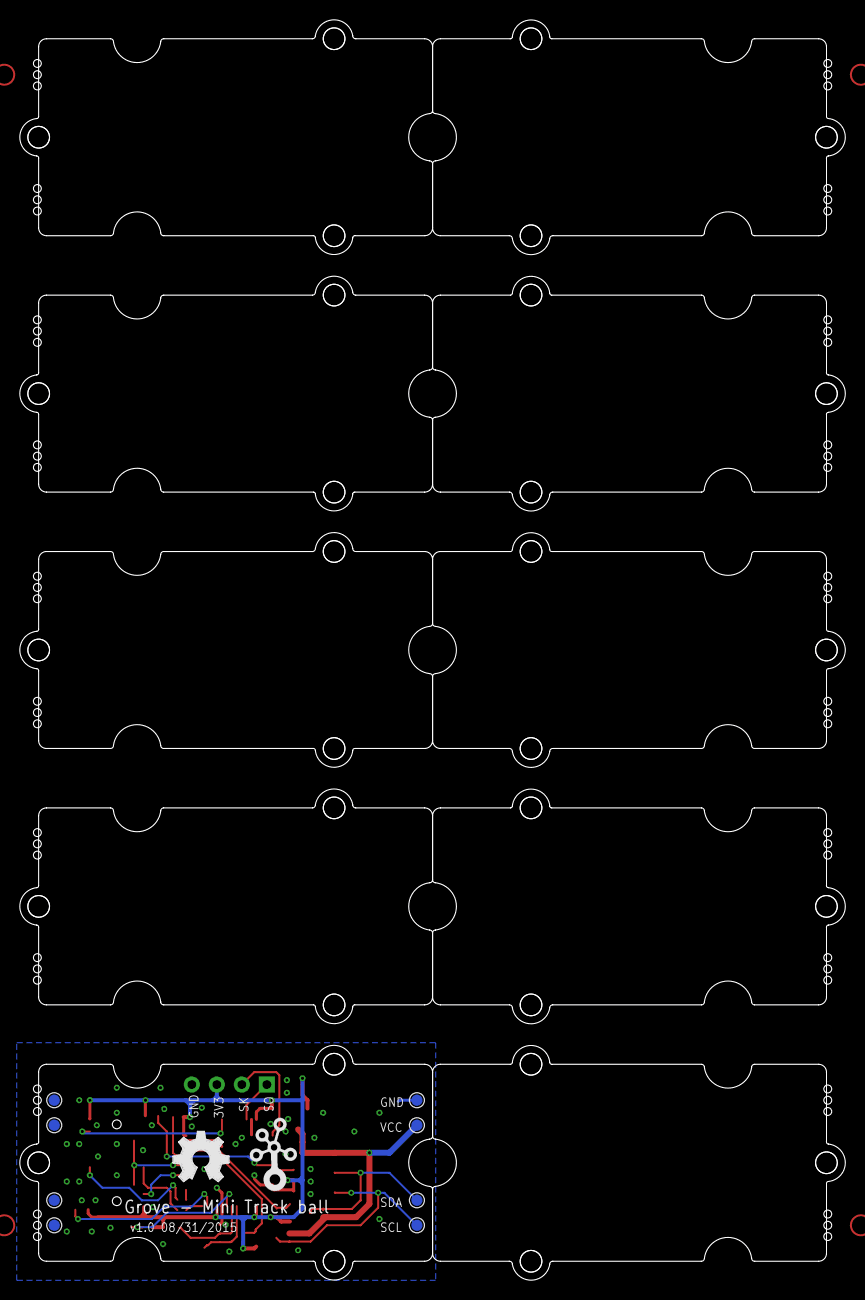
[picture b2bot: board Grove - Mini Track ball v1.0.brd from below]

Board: 2 copper layers, 83.8 x 128.0 mm, 63 parts (10 on the bottom side), 23 nets.

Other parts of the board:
U$1, U$2, U$3, U$4, U$5, U$6, U$9, U$10, U$11, U$12: GROVE-1*2-TEST-PLATFORM
U$7: GROVE-SILK-BIG
U$8: OSHW_FILLX200_NOTEXT

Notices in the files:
parts and their libraries:
moudle-new: This work is licensed under the Creative Commons Attribution 4.0 International License.
To view a copy of this license,visit:
http://creativecommons.org/licenses/by-sa/4.0
moudle-new: CC-BY-SA
